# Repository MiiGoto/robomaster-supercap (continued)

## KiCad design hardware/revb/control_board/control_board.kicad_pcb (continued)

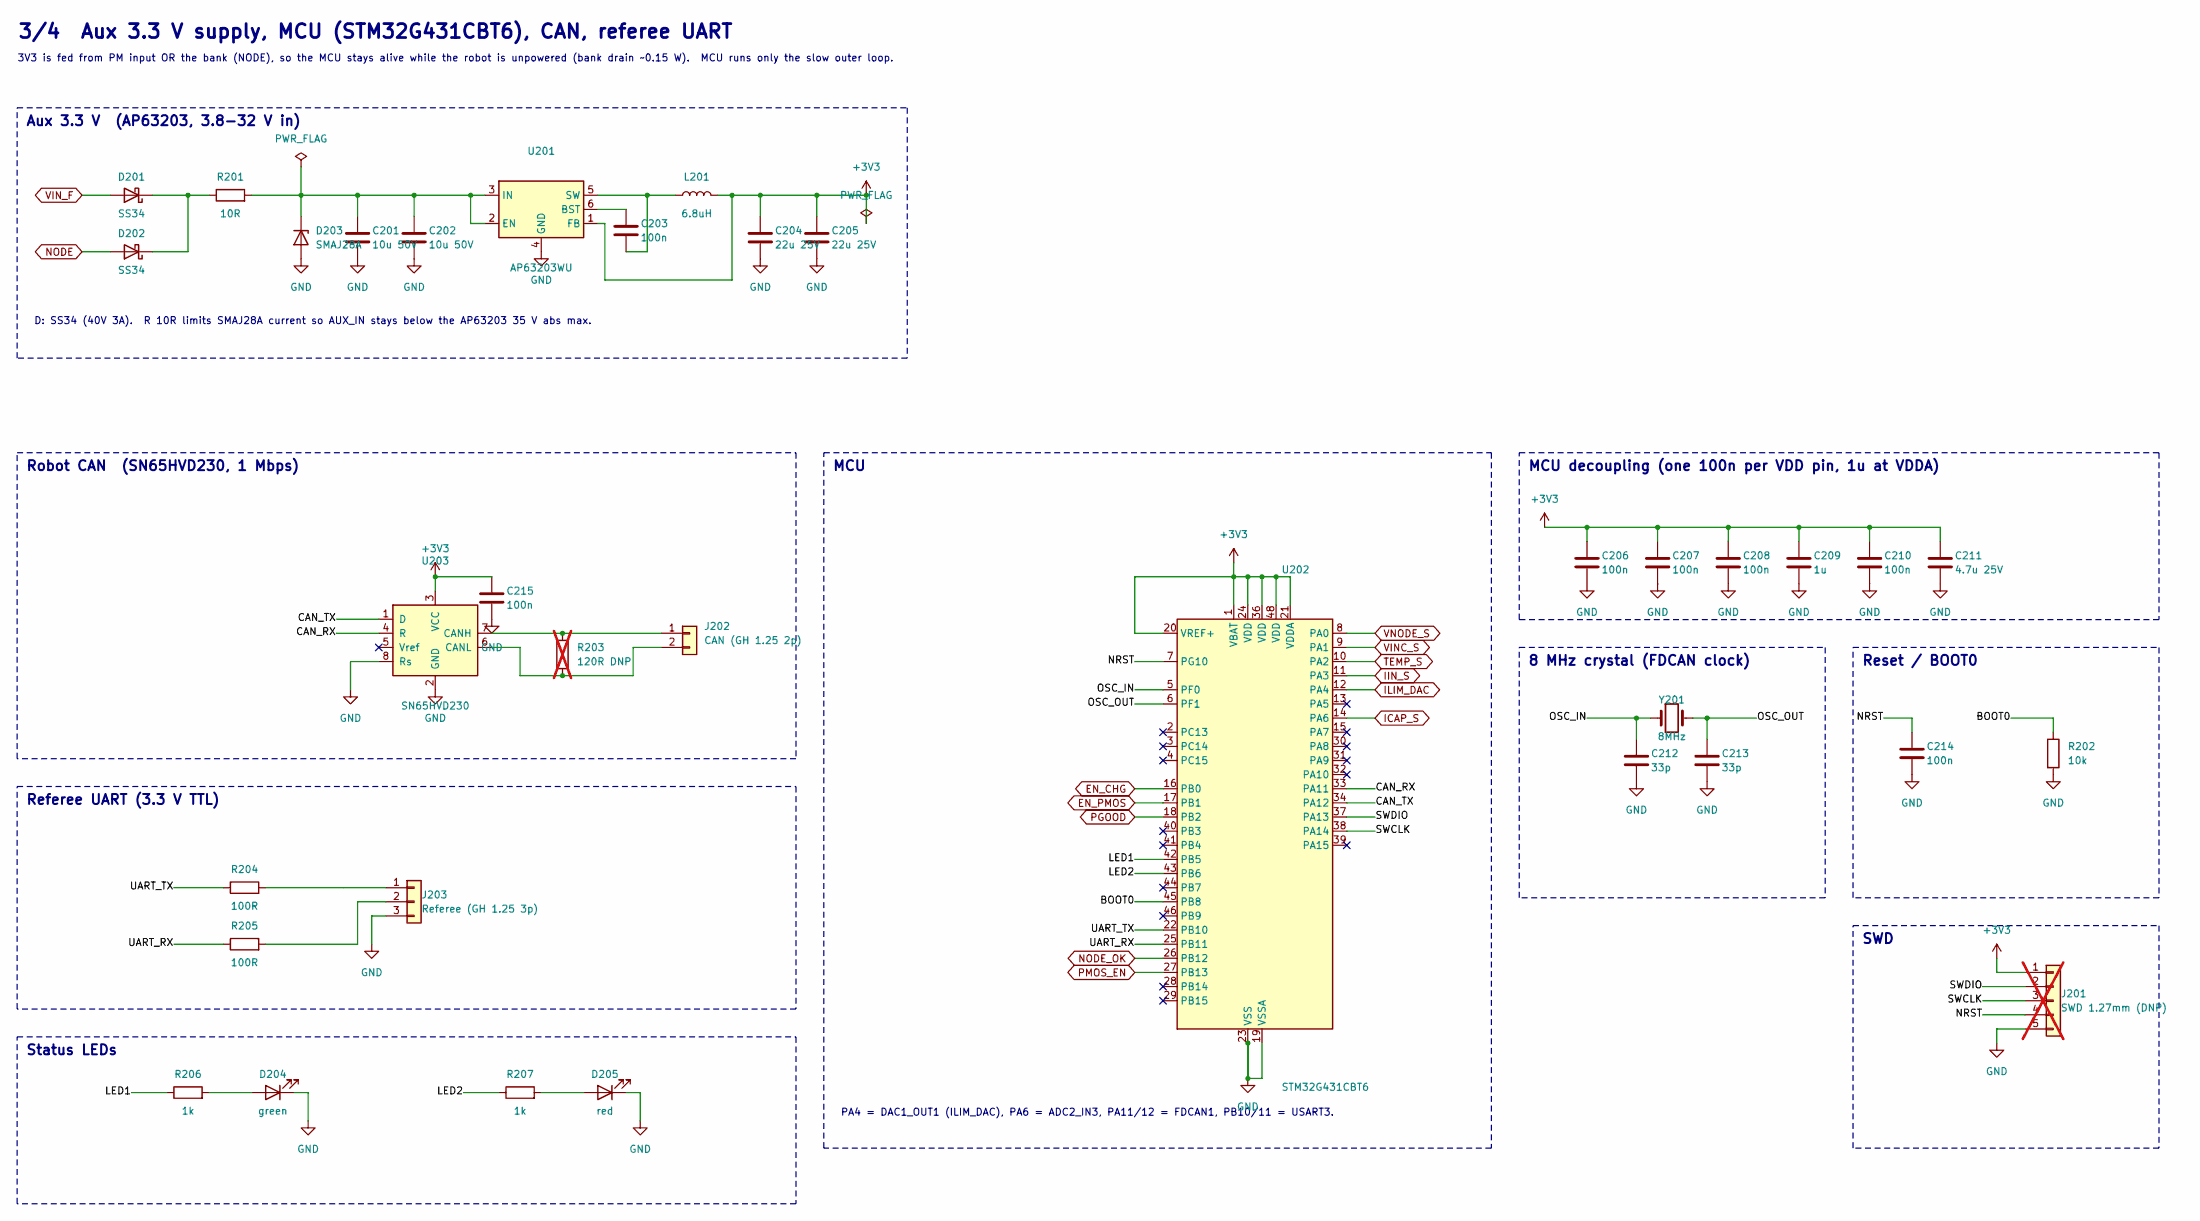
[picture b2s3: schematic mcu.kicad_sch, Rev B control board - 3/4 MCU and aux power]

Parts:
C201, C202: 10u 50V; C_1206_3216Metric; LCSC C13585
C203, C206, C207, C208, C210, C214, C215: 100n; C_0402_1005Metric; LCSC C1525
C204, C205: 22u 25V; C_0805_2012Metric; LCSC C45783
C209: 1u; C_0402_1005Metric; LCSC C52923
C211: 4.7u 25V; C_0805_2012Metric; LCSC C1779
C212, C213: 33p; C_0402_1005Metric; LCSC C1562
D201, D202: SS34; D_SMA; LCSC C8678
D203: SMAJ28A; D_SMA; LCSC C19077545
D204: green; LED_0603_1608Metric; LCSC C12624
D205: red; LED_0603_1608Metric; LCSC C2286
J201: SWD 1.27mm (DNP); PinHeader_1x05_P1.27mm_Vertical; not fitted
J202: CAN (GH 1.25 2p); JST_GH_SM02B-GHS-TB_1x02-1MP_P1.25mm_Horizontal; LCSC C225125
J203: Referee (GH 1.25 3p); JST_GH_SM03B-GHS-TB_1x03-1MP_P1.25mm_Horizontal; LCSC C225126
L201: 6.8uH; L_Wuerth_MAPI-4030; LCSC C167876
R201: 10R; R_0402_1005Metric; LCSC C25077
R202: 10k; R_0402_1005Metric; LCSC C25744
R203: 120R DNP; R_0402_1005Metric; LCSC C25079; not fitted
R204, R205: 100R; R_0402_1005Metric; LCSC C25076
R206, R207: 1k; R_0402_1005Metric; LCSC C11702
U201: AP63203WU; TSOT-23-6; LCSC C780769
U202: STM32G431CBT6; LQFP-48_7x7mm_P0.5mm; LCSC C529355
U203: SN65HVD230; SOIC-8_3.9x4.9mm_P1.27mm; LCSC C12084
Y201: 8MHz; Crystal_SMD_5032-2Pin_5.0x3.2mm; LCSC C115962

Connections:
+3V3: C204.1, C205.1, C206.1, C207.1, C208.1, C209.1, C210.1, C211.1, C215.1, J201.1, L201.2, U201.1 (FB), U202.1 (VBAT), U202.20 (VREF+), U202.21 (VDDA), U202.24 (VDD), U202.36 (VDD), U202.48 (VDD), U203.3 (VCC); also elsewhere on the board
/mcu/BOOT0: R202.1, U202.45 (PB8)
/mcu/CAN_RX: U202.33 (PA11), U203.4 (R)
/mcu/CAN_TX: U202.34 (PA12), U203.1 (D)
/mcu/LED1: R206.1, U202.42 (PB5)
/mcu/LED2: R207.1, U202.43 (PB6)
/mcu/NRST: C214.1, J201.4, U202.7 (PG10)
/mcu/OSC_IN: C212.1, U202.5 (PF0), Y201.1
/mcu/OSC_OUT: C213.1, U202.6 (PF1), Y201.2
/mcu/SWCLK: J201.3, U202.38 (PA14)
/mcu/SWDIO: J201.2, U202.37 (PA13)
/mcu/UART_RX: R205.1, U202.25 (PB11)
/mcu/UART_TX: R204.1, U202.22 (PB10)
EN_CHG: U202.16 (PB0); also elsewhere on the board
EN_PMOS: U202.17 (PB1); also elsewhere on the board
GND: C201.2, C202.2, C204.2, C205.2, C206.2, C207.2, C208.2, C209.2, C210.2, C211.2, C212.2, C213.2, C214.2, C215.2, D203.2 (A), D204.1 (K), D205.1 (K), J201.5, J203.3, R202.2, U201.4 (GND), U202.19 (VSSA), U202.23 (VSS), U202.35 (VSS), U202.47 (VSS), U203.2 (GND), U203.8 (Rs); also elsewhere on the board
ICAP_S: U202.14 (PA6); also elsewhere on the board
IIN_S: U202.11 (PA3); also elsewhere on the board
ILIM_DAC: U202.12 (PA4); also elsewhere on the board
NODE: D202.2 (A); also elsewhere on the board
NODE_OK: U202.26 (PB12); also elsewhere on the board
unnamed: D201.1 (K), D202.1 (K), R201.1
unnamed: C201.1, C202.1, D203.1 (K), R201.2, U201.2 (EN), U201.3 (IN)
unnamed: D204.2 (A), R206.2
unnamed: D205.2 (A), R207.2
unnamed: J202.1, R203.1, U203.7 (CANH)
unnamed: J202.2, R203.2, U203.6 (CANL)
unnamed: J203.1, R204.2
unnamed: J203.2, R205.2
unnamed: C203.1, U201.6 (BST)
unnamed: C203.2, L201.1, U201.5 (SW)
PGOOD: U202.18 (PB2); also elsewhere on the board
PMOS_EN: U202.27 (PB13); also elsewhere on the board
TEMP_S: U202.10 (PA2); also elsewhere on the board
VINC_S: U202.9 (PA1); also elsewhere on the board
VIN_F: D201.2 (A); also elsewhere on the board
VNODE_S: U202.8 (PA0); also elsewhere on the board

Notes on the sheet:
3/4 Aux 3.3 V supply, MCU (STM32G431CBT6), CAN, referee UART
3V3 is fed from PM input OR the bank (NODE), so the MCU stays alive while the robot is unpowered (bank drain ~0.15 W). MCU runs only the slow outer loop.
Aux 3.3 V (AP63203, 3.8-32 V in)
D: SS34 (40V 3A). R 10R limits SMAJ28A current so AUX_IN stays below the AP63203 35 V abs max.
MCU
PA4 = DAC1_OUT1 (ILIM_DAC), PA6 = ADC2_IN3, PA11/12 = FDCAN1, PB10/11 = USART3.
MCU decoupling (one 100n per VDD pin, 1u at VDDA)
8 MHz crystal (FDCAN clock)
Reset / BOOT0
SWD
Robot CAN (SN65HVD230, 1 Mbps)
Referee UART (3.3 V TTL)
Status LEDs

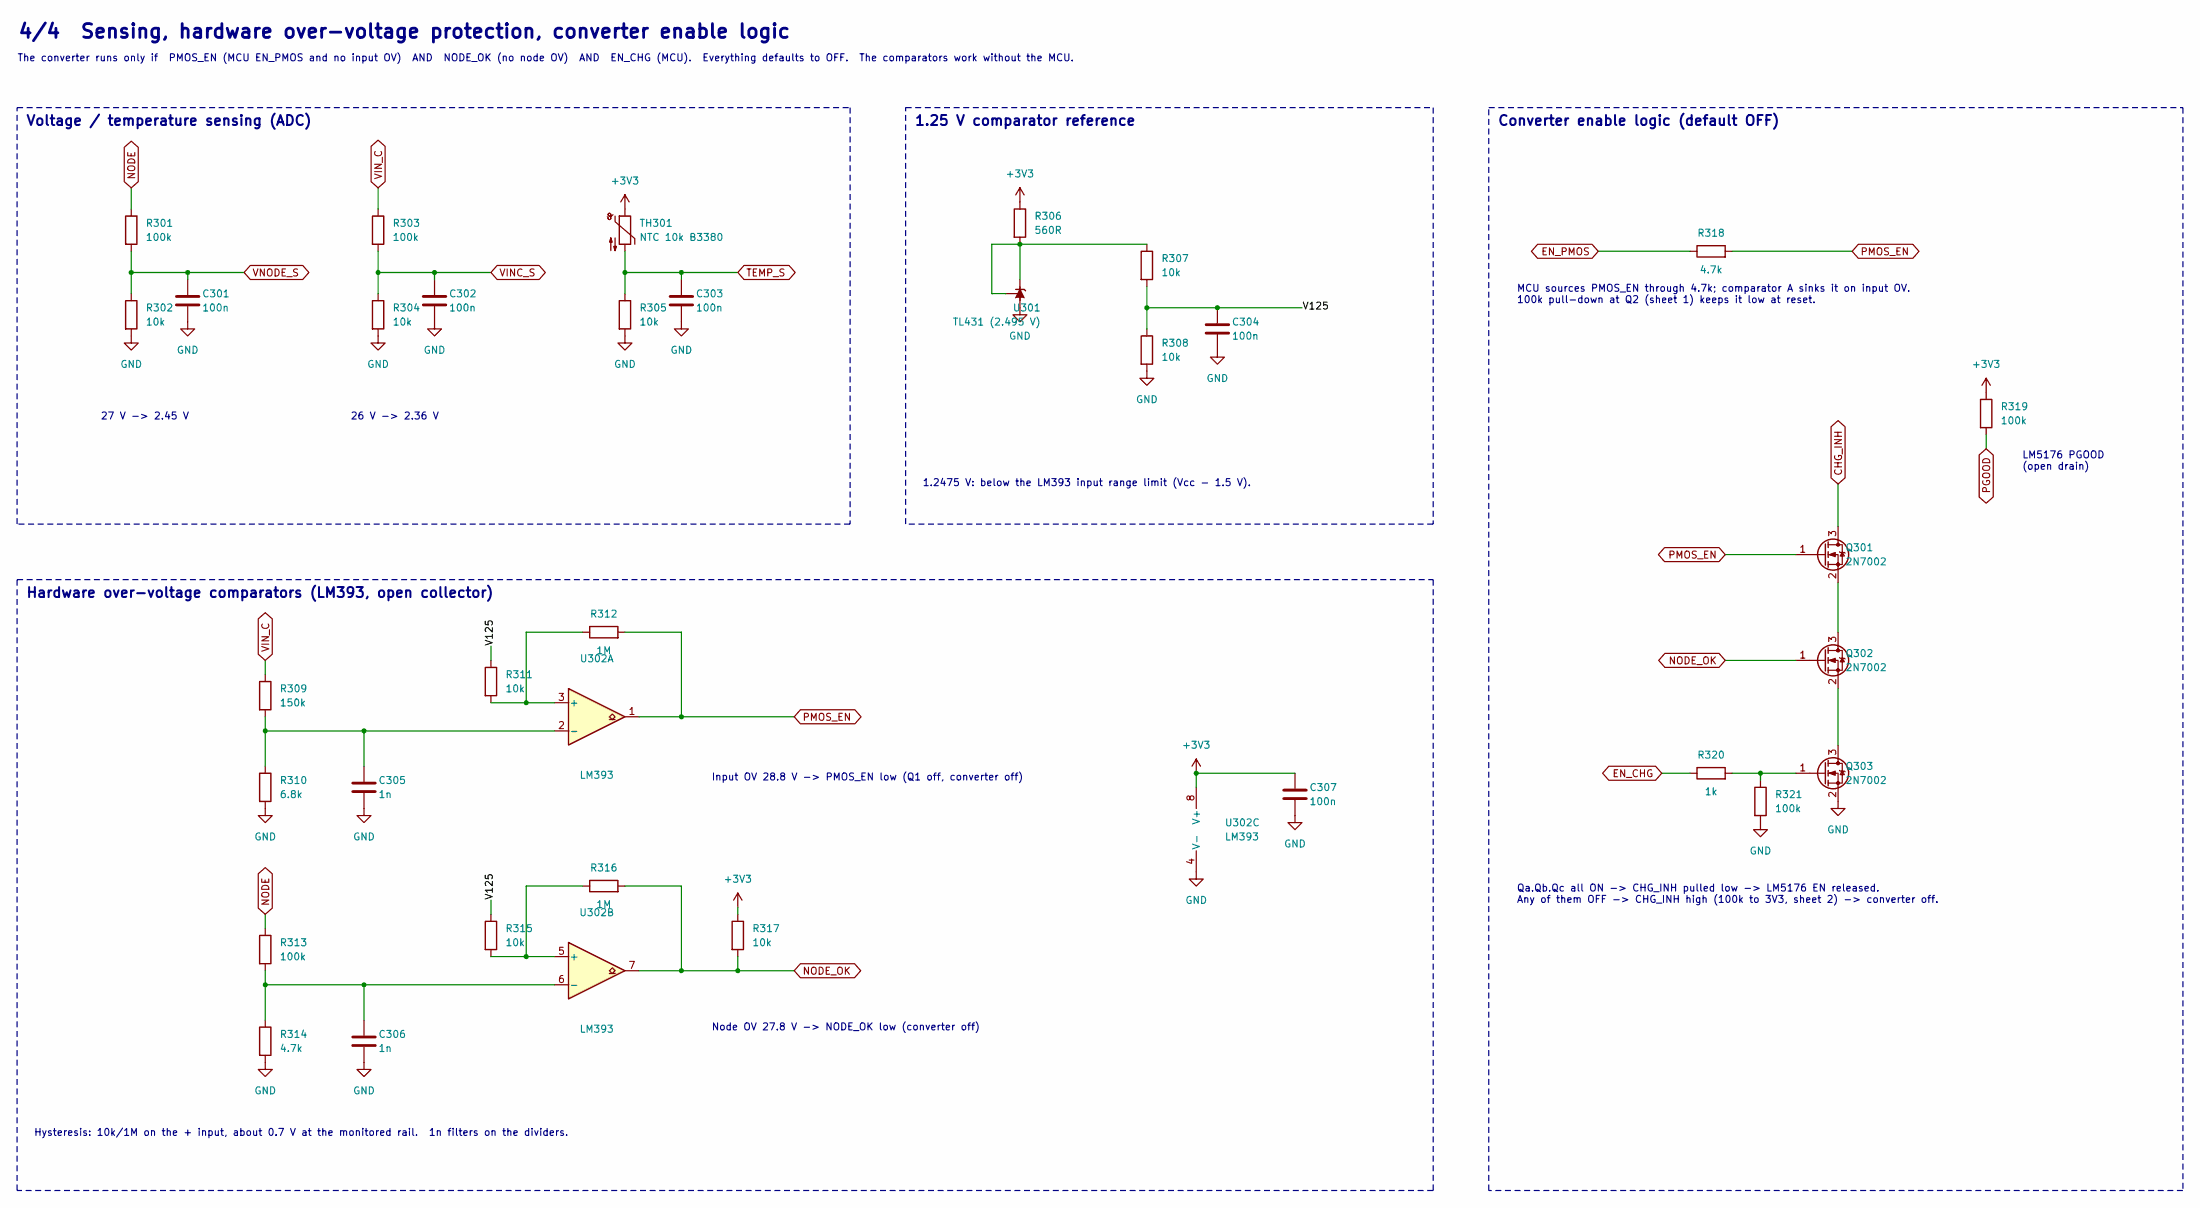
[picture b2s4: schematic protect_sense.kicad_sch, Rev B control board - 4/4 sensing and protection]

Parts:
C301, C302, C303, C304, C307: 100n; C_0402_1005Metric; LCSC C1525
C305, C306: 1n; C_0402_1005Metric; LCSC C1523
Q301, Q302, Q303: 2N7002; SOT-23; LCSC C8545
R301, R303, R313, R319, R321: 100k; R_0402_1005Metric; LCSC C25741
R302, R304, R305, R307, R308, R311, R315, R317: 10k; R_0402_1005Metric; LCSC C25744
R306: 560R; R_0603_1608Metric; LCSC C23204
R309: 150k; R_0402_1005Metric; LCSC C25755
R310: 6.8k; R_0402_1005Metric; LCSC C25917
R312, R316: 1M; R_0402_1005Metric; LCSC C26083
R314, R318: 4.7k; R_0402_1005Metric; LCSC C25900
R320: 1k; R_0402_1005Metric; LCSC C11702
TH301: NTC 10k B3380; R_0603_1608Metric; LCSC C13564
U301: TL431 (2.495 V); SOT-23; LCSC C181103
U302: LM393; SOIC-8_3.9x4.9mm_P1.27mm; LCSC C7955

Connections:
+3V3: C307.1, R306.1, R317.1, R319.1, TH301.1, U302.8 (V+); also elsewhere on the board
/protect/V125: C304.1, R307.2, R308.1, R311.1, R315.1
CHG_INH: Q301.3 (D); also elsewhere on the board
EN_CHG: R320.1; also elsewhere on the board
EN_PMOS: R318.1; also elsewhere on the board
GND: C301.2, C302.2, C303.2, C304.2, C305.2, C306.2, C307.2, Q303.2 (S), R302.2, R304.2, R305.2, R308.2, R310.2, R314.2, R321.2, U301.3 (A), U302.4 (V-); also elsewhere on the board
NODE: R301.1, R313.1; also elsewhere on the board
NODE_OK: Q302.1 (G), R316.2, R317.2, U302.7; also elsewhere on the board
unnamed: Q301.2 (S), Q302.3 (D)
unnamed: Q302.2 (S), Q303.3 (D)
unnamed: Q303.1 (G), R320.2, R321.1
unnamed: R306.2, R307.1, U301.1 (K), U301.2 (REF)
unnamed: R311.2, R312.1, U302.3 (+)
unnamed: C305.1, R309.2, R310.1, U302.2 (-)
unnamed: R315.2, R316.1, U302.5 (+)
unnamed: C306.1, R313.2, R314.1, U302.6 (-)
PGOOD: R319.2; also elsewhere on the board
PMOS_EN: Q301.1 (G), R312.2, R318.2, U302.1; also elsewhere on the board
TEMP_S: C303.1, R305.1, TH301.2; also elsewhere on the board
VINC_S: C302.1, R303.2, R304.1; also elsewhere on the board
VIN_C: R303.1, R309.1; also elsewhere on the board
VNODE_S: C301.1, R301.2, R302.1; also elsewhere on the board

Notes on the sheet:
4/4 Sensing, hardware over-voltage protection, converter enable logic
The converter runs only if PMOS_EN (MCU EN_PMOS and no input OV) AND NODE_OK (no node OV) AND EN_CHG (MCU). Everything defaults to OFF. The comparators work without the MCU.
Voltage / temperature sensing (ADC)
27 V -> 2.45 V
26 V -> 2.36 V
1.25 V comparator reference
1.2475 V: below the LM393 input range limit (Vcc - 1.5 V).
Hardware over-voltage comparators (LM393, open collector)
Input OV 28.8 V -> PMOS_EN low (Q1 off, converter off)
Node OV 27.8 V -> NODE_OK low (converter off)
Hysteresis: 10k/1M on the + input, about 0.7 V at the monitored rail. 1n filters on the dividers.
Converter enable logic (default OFF)
MCU sources PMOS_EN through 4.7k; comparator A sinks it on input OV. 100k pull-down at Q2 (sheet 1) keeps it low at reset.
LM5176 PGOOD (open drain)
Qa.Qb.Qc all ON -> CHG_INH pulled low -> LM5176 EN released. Any of them OFF -> CHG_INH high (100k to 3V3, sheet 2) -> converter off.

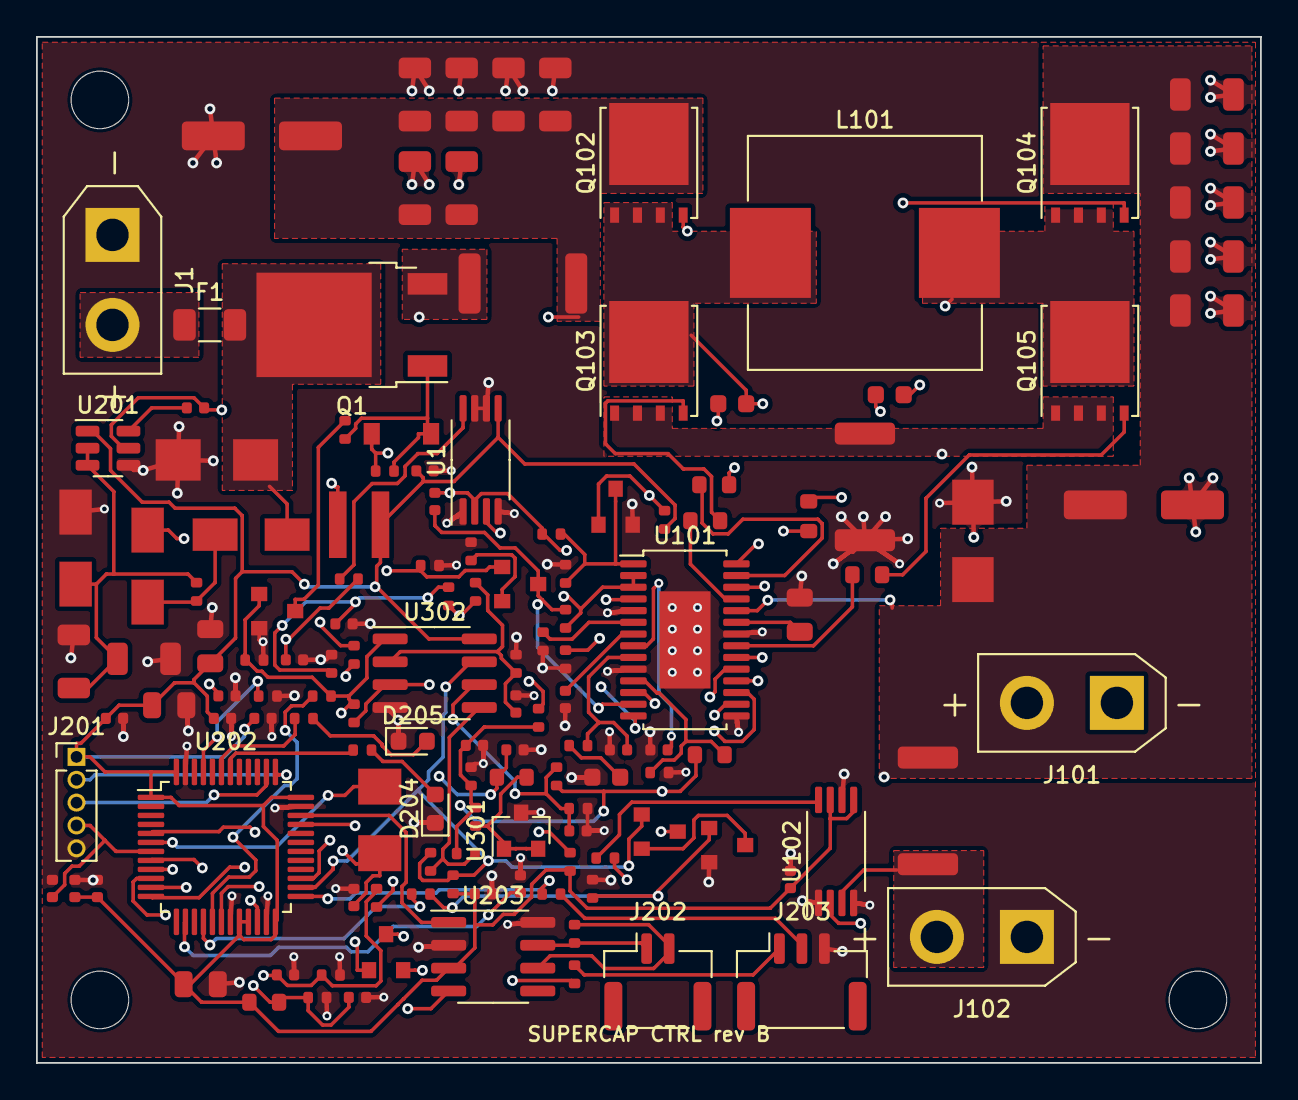
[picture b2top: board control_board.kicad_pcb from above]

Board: 4 copper layers, 68.0 x 57.0 mm, 140 parts (0 on the bottom side), 80 nets.

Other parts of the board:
H1, H2, H3: MountingHole_3.2mm_M3

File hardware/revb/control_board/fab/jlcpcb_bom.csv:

Comment,Designator,Footprint,LCSC Part #
LM5176PWPR,U101,HTSSOP-28-1EP_4.4x9.7mm_P0.65mm_EP2.85x5.4mm,C442493
220k,R101,R_0402_1005Metric,C25767
15k,R102,R_0402_1005Metric,C25756
2N7002,"Q101,Q2,Q301,Q302,Q303",SOT-23,C8545
100k,"R103,R1,R3,R8,R301,R303,R313,R319,R321",R_0402_1005Metric,C25741
200k,R104,R_0402_1005Metric,C25764
33k,R105,R_0402_1005Metric,C25779
220p,C101,C_0402_1005Metric,C1530
100n,"C102,C114,C203,C206,C207,C208,C210,C214,C215,C8,C9,C301,C302,C303,C304,C307",C_0402_1005Metric,C1525
470p,C103,C_0402_1005Metric,C1537
10k,"R106,R202,R2,R302,R304,R305,R307,R308,R311,R315,R317",R_0402_1005Metric,C25744
33n,C104,C_0603_1608Metric,C21117
1.5M,R107,R_0603_1608Metric,C4172
47k,R108,R_0402_1005Metric,C25792
4.7u 25V,"C105,C211",C_0805_2012Metric,C1779
2R2,"R109,R110,R111,R112",R_0603_1608Metric,C22939
100n 50V,"C106,C107",C_0603_1608Metric,C14663
NTMFS5C670NL,"Q102,Q103,Q104,Q105",TDSON-8-1,C179626
10uH,L101,L_Wuerth_HCI-1365,C242228
12m 2512,"R113,R4",R_2512_6332Metric,C49164692
4.7u,"C108,C109,C110,C111,C112,C1,C2,C3,C4,C5,C6",C_1206_3216Metric,C29823
100u,"C113,C7",CP_Elec_6.3x7.7,C3151829
SMBJ30A,"D101,D1",D_SMB,C19077584
XT30 chassis,J101,AMASS_XT30UPB-M_1x02_P5.0mm_Vertical,C428721
2m 2512,R114,R_2512_6332Metric,C7420017
XT30 to CM01/bank,J102,AMASS_XT30UPB-M_1x02_P5.0mm_Vertical,C428721
INA240A1PW,"U102,U1",TSSOP-8_4.4x3mm_P0.65mm,C93965
1k,"R115,R206,R207,R7,R9,R320",R_0402_1005Metric,C11702
1n,"C115,C10,C305,C306",C_0402_1005Metric,C1523
SS34,"D201,D202",D_SMA,C8678
10R,R201,R_0402_1005Metric,C25077
AP63203WU,U201,TSOT-23-6,C780769
SMAJ28A,D203,D_SMA,C19077545
10u 50V,"C201,C202",C_1206_3216Metric,C13585
6.8uH,L201,L_Wuerth_MAPI-4030,C167876
22u 25V,"C204,C205",C_0805_2012Metric,C45783
STM32G431CBT6,U202,LQFP-48_7x7mm_P0.5mm,C529355
1u,C209,C_0402_1005Metric,C52923
8MHz,Y201,Crystal_SMD_5032-2Pin_5.0x3.2mm,C115962
33p,"C212,C213",C_0402_1005Metric,C1562
SN65HVD230,U203,SOIC-8_3.9x4.9mm_P1.27mm,C12084
CAN (GH 1.25 2p),J202,JST_GH_SM02B-GHS-TB_1x02-1MP_P1.25mm_Horizontal,C225125
100R,"R204,R205,R5",R_0402_1005Metric,C25076
Referee (GH 1.25 3p),J203,JST_GH_SM03B-GHS-TB_1x03-1MP_P1.25mm_Horizontal,C225126
green,D204,LED_0603_1608Metric,C12624
red,D205,LED_0603_1608Metric,C2286
XT30,J1,AMASS_XT30UPB-M_1x02_P5.0mm_Vertical,C428721
10A,F1,Fuse_1206_3216Metric,C52988557
AOD409,Q1,TO-252-2,C36220
12V,D2,D_SOD-123,C19077426
MMBT5551,Q3,SOT-23,C2145
6.8k,"R6,R310",R_0402_1005Metric,C25917
NTC 10k B3380,TH301,R_0603_1608Metric,C13564
560R,R306,R_0603_1608Metric,C23204
TL431 (2.495 V),U301,SOT-23,C181103
LM393,U302,SOIC-8_3.9x4.9mm_P1.27mm,C7955
150k,R309,R_0402_1005Metric,C25755
1M,"R312,R316",R_0402_1005Metric,C26083
4.7k,"R314,R318",R_0402_1005Metric,C25900

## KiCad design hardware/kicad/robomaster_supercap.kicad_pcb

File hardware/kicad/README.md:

# Task 2 same-project update

robomaster_supercap.kicad_proを継続使用。root UUIDと既存sheet UUIDを維持しPRECHARGEを追加、9 concept pages。各sheetにblock interfaceの説明を更新。POWER_STAGEは四switch概念textのみでMOSFET/driver/L部品・netsなし、electrical connectivity未実装。PCB/project設定はTask1から変更なし。
ERC成功はhierarchy読み込み確認のみ。部品ratings/pin/機能/safety検証ではない。

---

## Task 1 record (historical; Task 2 above takes precedence)

# KiCad skeleton

Open `robomaster_supercap.kicad_pro` with KiCad 10.0.6。
rootと7 hierarchy pages: CONTROLLER / POWER_INPUT / SUPERCAP_BANK / POWER_STAGE / SENSING / CAN / SAFETY。
説明textのみ。部品、pin、electrical nets、MOSFET、driver、inductor、connector定格の実装なし。
PCBは空のplaceholder。outline、footprint、track、zoneなし。厚さ等のKiCad defaultは承認済み製造仕様ではない。
ERCはparser/hierarchy確認であり電気安全や配線の検証ではない。空boardのDRCはoutlineがない等の未実装結果をexpected limitationとして記録する。
generatorは新規targetのみ作成し既存fileがあれば拒否。通常編集はKiCadで行い、generator再実行で上書きしない。

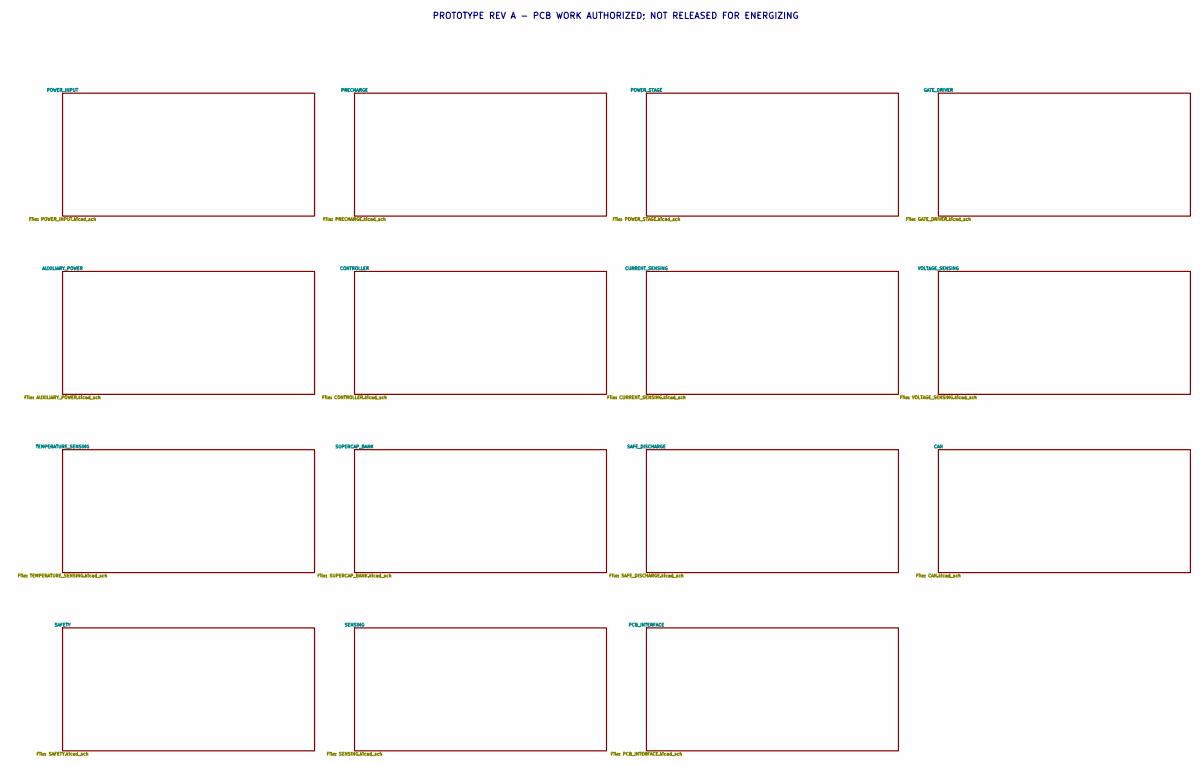
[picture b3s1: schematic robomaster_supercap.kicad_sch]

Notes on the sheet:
PROTOTYPE REV A - PCB WORK AUTHORIZED; NOT RELEASED FOR ENERGIZING

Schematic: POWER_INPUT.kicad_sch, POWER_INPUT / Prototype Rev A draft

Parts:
D1: SMBJ28A / no surge-energy guarantee; D_SMB; MPN SMBJ28A
D2: SMBJ18CA bidirectional coil suppression / release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; D_SMB; MPN SMBJ18CA
F1: 0997010.WXN / MINI997 58V10A / external 0FHM0002Z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; MPN 0997010.WXN
F2: 0997005.WXN / MINI997 58V5A / external 0FHM0002ZX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; MPN 0997005.WXN
J1: ROBOT BUS / external covered bolted power termina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
J2: BUS_ISO actuator+reserved diagnostic / no intrins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
J3: referee permit interface / no bypass
K1: BUS_ISO external NO contact / AEV14012 bench sele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; MPN AEV14012
Q1: CSD18540Q5B; VSONP-8-1EP_5x6_P1.27mm; MPN CSD18540Q5B
Q2: BC857B; SOT-23; MPN BC857B,215
Q3: BC847B; SOT-23; MPN BC847B,215
R1, R2, R3, R7, R8: 10k; R_0805_2012Metric; MPN CRCW080510K0FKEA
R4: 4.7k; R_0805_2012Metric; MPN CRCW08054K70FKEA
R5: 100k; R_0805_2012Metric; MPN CRCW0805100KFKEA
R6: 47R; R_0805_2012Metric; MPN CRCW080547R0FKEA
U1: Blue Sea6006 / external manual source disconnect;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; MPN 6006
U2: DDR-60L-12 / external bench actuator supply; MPN DDR-60L-12

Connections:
ACTUATOR_12V: D2.1 (K), J2.1, K1.3 (COIL_P), Q2.2 (E), R2.2 (B), U2.3 (VO_P), U2.4 (VO_P); also elsewhere on the board
BUS_FUSED: D1.1 (K), F1.2 (B), K1.1 (COM); also elsewhere on the board
BUS_ISO_COIL_GATE: Q1.2 (G_DS4), R1.1 (A), R6.2 (B)
BUS_ISO_COIL_M: D2.2 (A), J2.2, K1.4 (COIL_M), Q1.3 (D_DS5_6_7_8); also elsewhere on the board
BUS_ISO_DRIVE: R4.1 (A); also elsewhere on the board
BUS_ISO_FB: J2.3, R7.1 (A); also elsewhere on the board
BUS_ISO_NPN_C: Q3.3 (C), R3.2 (B)
BUS_ISO_NPN_C_BASE: Q3.1 (B), R4.2 (B), R5.1 (A)
BUS_ISO_PNP_B: Q2.1 (B), R2.1 (A), R3.1 (A)
BUS_ISO_PNP_C: Q2.3 (C), R6.1 (A)
GND: D1.2 (A), J1.2, J2.4, J3.2, Q1.1 (S_DS1_2_3), Q3.2 (E), R1.2 (B), R5.2 (B), R7.2 (B), R8.2 (B), U2.1 (VO_M), U2.2 (VO_M), U2.6 (VIN_M); also elsewhere on the board
unnamed: F1.1 (A), F2.1 (A), J3.1, U1.2 (SWITCHED)
unnamed: F2.2 (B), U2.5 (VIN_P)
unnamed: J1.1, U1.1 (COM)
REFEREE_PERMIT: J3.3, R8.1 (A); also elsewhere on the board

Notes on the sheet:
Aux input is BUS_FUSED upstream of NO isolate. No bank-fed control rail.
Four AEV14012 main/bypass contacts, 12V coils; external DDR-60L-12. Bench only: total contact mass about1.6kg.
Fuse+TVS values provisional. TVS cathode positive; reverse insertion is not authorized.

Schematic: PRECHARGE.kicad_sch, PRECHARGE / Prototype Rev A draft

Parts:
D3, D4: SMBJ18CA bidirectional coil suppression / release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; D_SMB; MPN SMBJ18CA
J4: BYP_BUS actuator+reserved diagnostic / no intrins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
J5: BYP_CAP actuator+reserved diagnostic / no intrins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
K2: BYP_BUS external NO contact / AEV14012 bench sele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; MPN AEV14012
K3: BYP_CAP external NO contact / AEV14012 bench sele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; MPN AEV14012
Q4, Q7, Q8, Q11: BC847B; SOT-23; MPN BC847B,215
Q5, Q9: CSD18540Q5B; VSONP-8-1EP_5x6_P1.27mm; MPN CSD18540Q5B
Q6, Q10: BC857B; SOT-23; MPN BC857B,215
R9, R21: 150R; R_0805_2012Metric; MPN CRCW0805150RFKEA
R10, R22: 1.5k; R_0805_2012Metric; MPN CRCW08051K50FKEA
R11, R12, R14, R15, R16, R20, R23, R24, R26, R27, R28, R32: 10k; R_0805_2012Metric; MPN CRCW080510K0FKEA
R13, R25: 100R / HS25 100R F / external chassis mount; MPN HS25 100R F
R17, R29: 4.7k; R_0805_2012Metric; MPN CRCW08054K70FKEA
R18, R30: 100k; R_0805_2012Metric; MPN CRCW0805100KFKEA
R19, R31: 47R; R_0805_2012Metric; MPN CRCW080547R0FKEA
U3, U4: AQZ202G / external precharge SSR; MPN AQZ202G

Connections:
ACTUATOR_12V: D3.1 (K), D4.1 (K), J4.1, J5.1, K2.3 (COIL_P), K3.3 (COIL_P), Q6.2 (E), Q10.2 (E), R15.2 (B), R27.2 (B); also elsewhere on the board
BYP_BUS_COIL_GATE: Q5.2 (G_DS4), R14.1 (A), R19.2 (B)
BYP_BUS_COIL_M: D3.2 (A), J4.2, K2.4 (COIL_M), Q5.3 (D_DS5_6_7_8); also elsewhere on the board
BYP_BUS_DRIVE: R17.1 (A); also elsewhere on the board
BYP_BUS_FB: J4.3, R20.1 (A); also elsewhere on the board
BYP_BUS_NPN_C: Q7.3 (C), R16.2 (B)
BYP_BUS_NPN_C_BASE: Q7.1 (B), R17.2 (B), R18.1 (A)
BYP_BUS_PNP_B: Q6.1 (B), R15.1 (A), R16.1 (A)
BYP_BUS_PNP_C: Q6.3 (C), R19.1 (A)
BYP_CAP_COIL_GATE: Q9.2 (G_DS4), R26.1 (A), R31.2 (B)
BYP_CAP_COIL_M: D4.2 (A), J5.2, K3.4 (COIL_M), Q9.3 (D_DS5_6_7_8); also elsewhere on the board
BYP_CAP_DRIVE: R29.1 (A); also elsewhere on the board
BYP_CAP_FB: J5.3, R32.1 (A); also elsewhere on the board
BYP_CAP_NPN_C: Q11.3 (C), R28.2 (B)
BYP_CAP_NPN_C_BASE: Q11.1 (B), R29.2 (B), R30.1 (A)
BYP_CAP_PNP_B: Q10.1 (B), R27.1 (A), R28.1 (A)
BYP_CAP_PNP_C: Q10.3 (C), R31.1 (A)
GND: J4.4, J5.4, Q4.2 (E), Q5.1 (S_DS1_2_3), Q7.2 (E), Q8.2 (E), Q9.1 (S_DS1_2_3), Q11.2 (E), R11.2 (B), R12.2 (B), R14.2 (B), R18.2 (B), R20.2 (B), R23.2 (B), R24.2 (B), R26.2 (B), R30.2 (B), R32.2 (B); also elsewhere on the board
unnamed: K2.1 (COM), U3.3 (ACDC_A)
unnamed: K2.2 (NO), R13.2 (B)
unnamed: K3.1 (COM), U4.3 (ACDC_A)
unnamed: K3.2 (NO), R25.2 (B)
unnamed: R13.1 (A), U3.4 (ACDC_B)
unnamed: R25.1 (A), U4.4 (ACDC_B)
PRE_BUS_DRIVE: R10.1 (A); also elsewhere on the board
PRE_BUS_FB: R12.1 (A); also elsewhere on the board
PRE_BUS_LED_M: Q4.3 (C), U3.1 (LED_M); also elsewhere on the board
PRE_BUS_LED_P: R9.2 (B), U3.2 (LED_P); also elsewhere on the board
PRE_BUS_SSR_BASE: Q4.1 (B), R10.2 (B), R11.1 (A)
PRE_CAP_DRIVE: R22.1 (A); also elsewhere on the board
PRE_CAP_FB: R24.1 (A); also elsewhere on the board
PRE_CAP_LED_M: Q8.3 (C), U4.1 (LED_M); also elsewhere on the board
PRE_CAP_LED_P: R21.2 (B), U4.2 (LED_P); also elsewhere on the board
PRE_CAP_SSR_BASE: Q8.1 (B), R22.2 (B), R23.1 (A)
V3V3: R9.1 (A), R21.1 (A); also elsewhere on the board

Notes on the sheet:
PRE_BUS SSR has no auxiliary contact: infer conduction using raw/link ADC; FB pin reserved LOW, not confirmation.
PRE_CAP SSR has no auxiliary contact: infer conduction using raw/link ADC; FB pin reserved LOW, not confirmation.
Separate NO isolate plus NO resistor-path and NO bypass contacts; no permanent path around isolation.
Six470uF per link; 26V/100R t95 nominal0.845s, worst target<1.1s. Timeout3s and delta-V<1V.
SSR path acceptance uses link voltage progression and open-path diagnosis; no resistor-only bank charge.

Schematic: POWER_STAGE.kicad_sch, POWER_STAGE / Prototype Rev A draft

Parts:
C1, C2, C3, C4, C5, C6, C9, C10, C11, C12, C13, C14: 470uF /63V EEUFR1J471 / ripple1.995Arms at100kHz; CP_Radial_D12.5mm_P5.00mm; MPN EEUFR1J471
C7, C8, C15, C16: 2.2uF / 100V X7R / effective C MUST VERIFY; C_1210_3225Metric; MPN GRM32ER72A225KA35L
C17, C18: 1nF /100V DNI tunable; C_0805_2012Metric; MPN C0805C102J1GACTU; not fitted
D5, D6, D7, D8: BZT52H-C15 / gate clamp candidate; D_SOD-123F; MPN BZT52H-C15
L1: XAL1510-223MED / 22uH +/-20%; L_Coilcraft_XAL1510-223; MPN XAL1510-223MED
Q12, Q13, Q14, Q15: CSD18540Q5B; VSONP-8-1EP_5x6_P1.27mm; MPN CSD18540Q5B
R33, R34, R35: WSK25123L000FEA / 3mR 1% 1W; R_Shunt_Vishay_WSK2512_6332Metric_T2.21mm; MPN WSK25123L000FEA
R36, R37, R38, R39: 10k GS mandatory; R_0805_2012Metric; MPN CRCW080510K0FKEA
R40, R41: 10R DNI tunable; R_0805_2012Metric; MPN CRCW080510R0FKEA; not fitted

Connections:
BUS_KELVIN_M: R33.3 (K_M); also elsewhere on the board
BUS_KELVIN_P: R33.2 (K_P); also elsewhere on the board
BUS_LINK: C1.1 (A), C2.1 (A), C3.1 (A), C4.1 (A), C5.1 (A), C6.1 (A), C7.1 (A), C8.1 (A), Q12.3 (D_DS5_6_7_8), R33.4 (I_M); also elsewhere on the board
BUS_LINK_IN: R33.1 (I_P); also elsewhere on the board
CAP_KELVIN_M: R34.3 (K_M); also elsewhere on the board
CAP_KELVIN_P: R34.2 (K_P); also elsewhere on the board
CAP_LINK: C9.1 (A), C10.1 (A), C11.1 (A), C12.1 (A), C13.1 (A), C14.1 (A), C15.1 (A), C16.1 (A), Q14.3 (D_DS5_6_7_8), R34.4 (I_M); also elsewhere on the board
CAP_LINK_IN: R34.1 (I_P); also elsewhere on the board
GATE_AH: D5.1 (K), Q12.2 (G_DS4), R36.1 (A); also elsewhere on the board
GATE_AL: D6.1 (K), Q13.2 (G_DS4), R37.1 (A); also elsewhere on the board
GATE_BH: D7.1 (K), Q14.2 (G_DS4), R38.1 (A); also elsewhere on the board
GATE_BL: D8.1 (K), Q15.2 (G_DS4), R39.1 (A); also elsewhere on the board
GND: C1.2 (B), C2.2 (B), C3.2 (B), C4.2 (B), C5.2 (B), C6.2 (B), C7.2 (B), C8.2 (B), C9.2 (B), C10.2 (B), C11.2 (B), C12.2 (B), C13.2 (B), C14.2 (B), C15.2 (B), C16.2 (B), C17.2 (B), C18.2 (B), D6.2 (A), D8.2 (A), Q13.1 (S_DS1_2_3), Q15.1 (S_DS1_2_3), R37.2 (B), R39.2 (B); also elsewhere on the board
IL_KELVIN_M: R35.3 (K_M); also elsewhere on the board
IL_KELVIN_P: R35.2 (K_P); also elsewhere on the board
IL_TO_L: L1.1 (A), R35.4 (I_M)
SW_NODE_A: D5.2 (A), Q12.1 (S_DS1_2_3), Q13.3 (D_DS5_6_7_8), R35.1 (I_P), R36.2 (B), R40.1 (A); also elsewhere on the board
SW_NODE_A_SNUB: C17.1 (A), R40.2 (B)
SW_NODE_B: D7.2 (A), L1.2 (B), Q14.1 (S_DS1_2_3), Q15.3 (D_DS5_6_7_8), R38.2 (B), R41.1 (A); also elsewhere on the board
SW_NODE_B_SNUB: C18.1 (A), R41.2 (B)

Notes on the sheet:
Body diode S -> D: healthy all-OFF positive rails block static DC; inductor decay or a short high-side FET can feed the other rail.
Shunts: power pads1/4, Kelvin pads2/3. WSK3mR terminal T=2.21mm (not the>=5mR T1.19 land).
Primary fs=200kHz; initial average current cap9.5A maximum,8A normal;12A remains later design goal.

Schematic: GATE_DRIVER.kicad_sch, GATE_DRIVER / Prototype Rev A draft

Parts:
C19, C22: 470nF /50V X7R bootstrap / effectiveC>=200nF targ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; C_0805_2012Metric; MPN GRM21BR71H474KA88L
C20, C23: 1uF /25V X7R; C_0805_2012Metric; MPN GRM21BR71H105KA12L
C21, C24, C26, C27: 100nF / 16V X7R; C_0805_2012Metric; MPN C0805C104K5RACTU
C25: 1nF EN filter; C_0805_2012Metric; MPN C0805C102J1GACTU
D9, D10, D11, D12: 1N4148W DNI turnoff bypass; D_SOD-123; MPN 1N4148W; not fitted
R42, R44, R48, R50: 4.7R gate / tunable; R_0603_1608Metric; MPN CRCW06034R70FNEA
R43, R45, R49, R51: 2.2R DNI turnoff option; R_0805_2012Metric; MPN CRCW08052R20FNEA; not fitted
R46, R47, R52, R53, R54: 10k; R_0805_2012Metric; MPN CRCW080510K0FKEA
U5, U6: UCC27282DRCR; VSON-10-1EP_3x3mm_P0.5mm_EP1.65x2.4mm; MPN UCC27282DRCR
U7, U8: SN74LVC2G08DCUR; VSSOP-8_2.3x2mm_P0.5mm; MPN SN74LVC2G08DCUR

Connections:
GATE_AH: D9.2 (A), R42.2 (B); also elsewhere on the board
GATE_AL: D10.2 (A), R44.2 (B); also elsewhere on the board
GATE_BH: D11.2 (A), R48.2 (B); also elsewhere on the board
GATE_BL: D12.2 (A), R50.2 (B); also elsewhere on the board
GATE_PERMIT: C25.1 (A), R54.1 (A), U5.6 (EN), U6.6 (EN), U7.2 (B1), U7.6 (B2), U8.2 (B1), U8.6 (B2); also elsewhere on the board
GND: C20.2 (B), C21.2 (B), C23.2 (B), C24.2 (B), C25.2 (B), C26.2 (B), C27.2 (B), R46.2 (B), R47.2 (B), R52.2 (B), R53.2 (B), R54.2 (B), U5.9 (VSS), U5.11 (EP), U6.9 (VSS), U6.11 (EP), U7.4 (GND), U8.4 (GND); also elsewhere on the board
HB_A: C19.1 (A), U5.3 (HB)
HB_B: C22.1 (A), U6.3 (HB)
HO_A: R42.1 (A), R43.1 (A), U5.4 (HO)
HO_A_FAST: D9.1 (K), R43.2 (B)
HO_B: R48.1 (A), R49.1 (A), U6.4 (HO)
HO_B_FAST: D11.1 (K), R49.2 (B)
LO_A: R44.1 (A), R45.1 (A), U5.10 (LO)
LO_A_FAST: D10.1 (K), R45.2 (B)
LO_B: R50.1 (A), R51.1 (A), U6.10 (LO)
LO_B_FAST: D12.1 (K), R51.2 (B)
PWM_AH: U7.1 (A1); also elsewhere on the board
PWM_AH_SAFE: R46.1 (A), U5.7 (HI), U7.7 (Y1)
PWM_AL: U7.5 (A2); also elsewhere on the board
PWM_AL_SAFE: R47.1 (A), U5.8 (LI), U7.3 (Y2)
PWM_BH: U8.1 (A1); also elsewhere on the board
PWM_BH_SAFE: R52.1 (A), U6.7 (HI), U8.7 (Y1)
PWM_BL: U8.5 (A2); also elsewhere on the board
PWM_BL_SAFE: R53.1 (A), U6.8 (LI), U8.3 (Y2)
SW_NODE_A: C19.2 (B), U5.5 (HS); also elsewhere on the board
SW_NODE_B: C22.2 (B), U6.5 (HS); also elsewhere on the board
V3V3: C26.1 (A), C27.1 (A), U7.8 (VCC), U8.8 (VCC); also elsewhere on the board
V12_DRIVER: C20.1 (A), C21.1 (A), C23.1 (A), C24.1 (A), U5.1 (VDD), U6.1 (VDD); also elsewhere on the board

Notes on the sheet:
DRC package only: EN pin6, exposed pad11 to VSS. Internal bootstrap diode used.
470nF is provisional: Qg53nC / Ceff200nF=0.265V plus bias/leak loss; both legs refresh each cycle.
No 100% high-side duty. Minimum off/refresh time and deadtime require gate-waveform validation.
Independent AND inhibit stops HI/LI; EN secondary (typ1.5us is not a maximum guarantee).

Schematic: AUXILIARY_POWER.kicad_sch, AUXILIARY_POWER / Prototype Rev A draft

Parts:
C28, C34: 2.2nF /50V X7R mandatory; C_0805_2012Metric; MPN C0805C222K5RACTU
C29, C35: 2.2uF /100V X7R; C_1210_3225Metric; MPN GRM32ER72A225KA35L
C30, C31, C36, C37: 22uF /25V X7R; C_1210_3225Metric; MPN C1210C226K3RACTU
C32, C38: 1nF C0G; C_0805_2012Metric; MPN C0805C102J1GACTU
C33, C39: 100pF C0G; C_0805_2012Metric; MPN C0805C101J1GACTU
L2: 68uH / MSS1246T-683MLB; L_Coilcraft_MSS1246T-XXX; MPN MSS1246T-683MLB
L3: 47uH / MSS1246T-473MLB; L_Coilcraft_MSS1246T-XXX; MPN MSS1246T-473MLB
R55: 909k; R_0805_2012Metric; MPN CRCW0805909KFKEA
R56, R57, R63: 100k; R_0805_2012Metric; MPN CRCW0805100KFKEA
R58, R61, R65: 1M; R_0805_2012Metric; MPN CRCW08051M00FKEA
R59, R66: 82.5k; R_0805_2012Metric; MPN CRCW080582K5FKEA
R60, R67: 10k; R_0805_2012Metric; MPN CRCW080510K0FKEA
R62: 174k; R_0805_2012Metric; MPN CRCW0805174KFKEA
R64: 27.4k; R_0805_2012Metric; MPN CRCW080527K4FKEA
R68: 475k; R_0805_2012Metric; MPN CRCW0805475KFKEA
U9, U10: LM5164DDAR; TI_SO-PowerPAD-8; MPN LM5164DDAR

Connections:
AUX_EN_DRV: R58.2 (B), R59.1 (A), U9.3 (EN)
AUX_EN_MCU: R65.2 (B), R66.1 (A), U10.3 (EN)
AUX_FB_DRV: C33.2 (B), R55.2 (B), R56.1 (A), U9.5 (FB)
AUX_FB_MCU: C39.2 (B), R62.2 (B), R63.1 (A), U10.5 (FB)
AUX_RIPPLE_DRV: C32.1 (A), C33.1 (A), R61.2 (B)
AUX_RIPPLE_MCU: C38.1 (A), C39.1 (A), R68.2 (B)
AUX_SW_DRV: C28.2 (B), L2.1 (A), R61.1 (A), U9.8 (SW)
AUX_SW_MCU: C34.2 (B), L3.1 (A), R68.1 (A), U10.8 (SW)
BST_DRV: C28.1 (A), U9.7 (BST)
BST_MCU: C34.1 (A), U10.7 (BST)
BUS_FUSED: C29.1 (A), C35.1 (A), R58.1 (A), R65.1 (A), U9.2 (VIN), U10.2 (VIN); also elsewhere on the board
GND: C29.2 (B), C30.2 (B), C31.2 (B), C35.2 (B), C36.2 (B), C37.2 (B), R56.2 (B), R57.2 (B), R59.2 (B), R63.2 (B), R64.2 (B), R66.2 (B), U9.1 (GND), U9.9 (EP), U10.1 (GND), U10.9 (EP); also elsewhere on the board
PG_DRV: R60.1 (A), U9.6 (PGOOD); also elsewhere on the board
PG_MCU: R67.1 (A), U10.6 (PGOOD); also elsewhere on the board
RON_DRV: R57.1 (A), U9.4 (RON)
RON_MCU: R64.1 (A), U10.4 (RON)
V3V3: C36.1 (A), C37.1 (A), C38.2 (B), L3.2 (B), R60.2 (B), R62.1 (A), R67.2 (B); also elsewhere on the board
V12_DRIVER: C30.1 (A), C31.1 (A), C32.2 (B), L2.2 (B), R55.1 (A); also elsewhere on the board

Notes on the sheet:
12V rail 1A IC capacity is not the available actuator/thermal budget. External contact coils require separate reviewed actuator supply.
3.3V and driver12V independently bus-fed, no bank-fed MCU rail. UVLO approx19.68V-on/18.37V-off.
COT Type3 ripple RA/CA/CB options: stability/startup/backfeed and actual auxiliary load must be verified.
Feedback:1.2*(1+909k/100k)=12.108V;1.2*(1+174k/100k)=3.288V. PGOOD qualified by safety.
